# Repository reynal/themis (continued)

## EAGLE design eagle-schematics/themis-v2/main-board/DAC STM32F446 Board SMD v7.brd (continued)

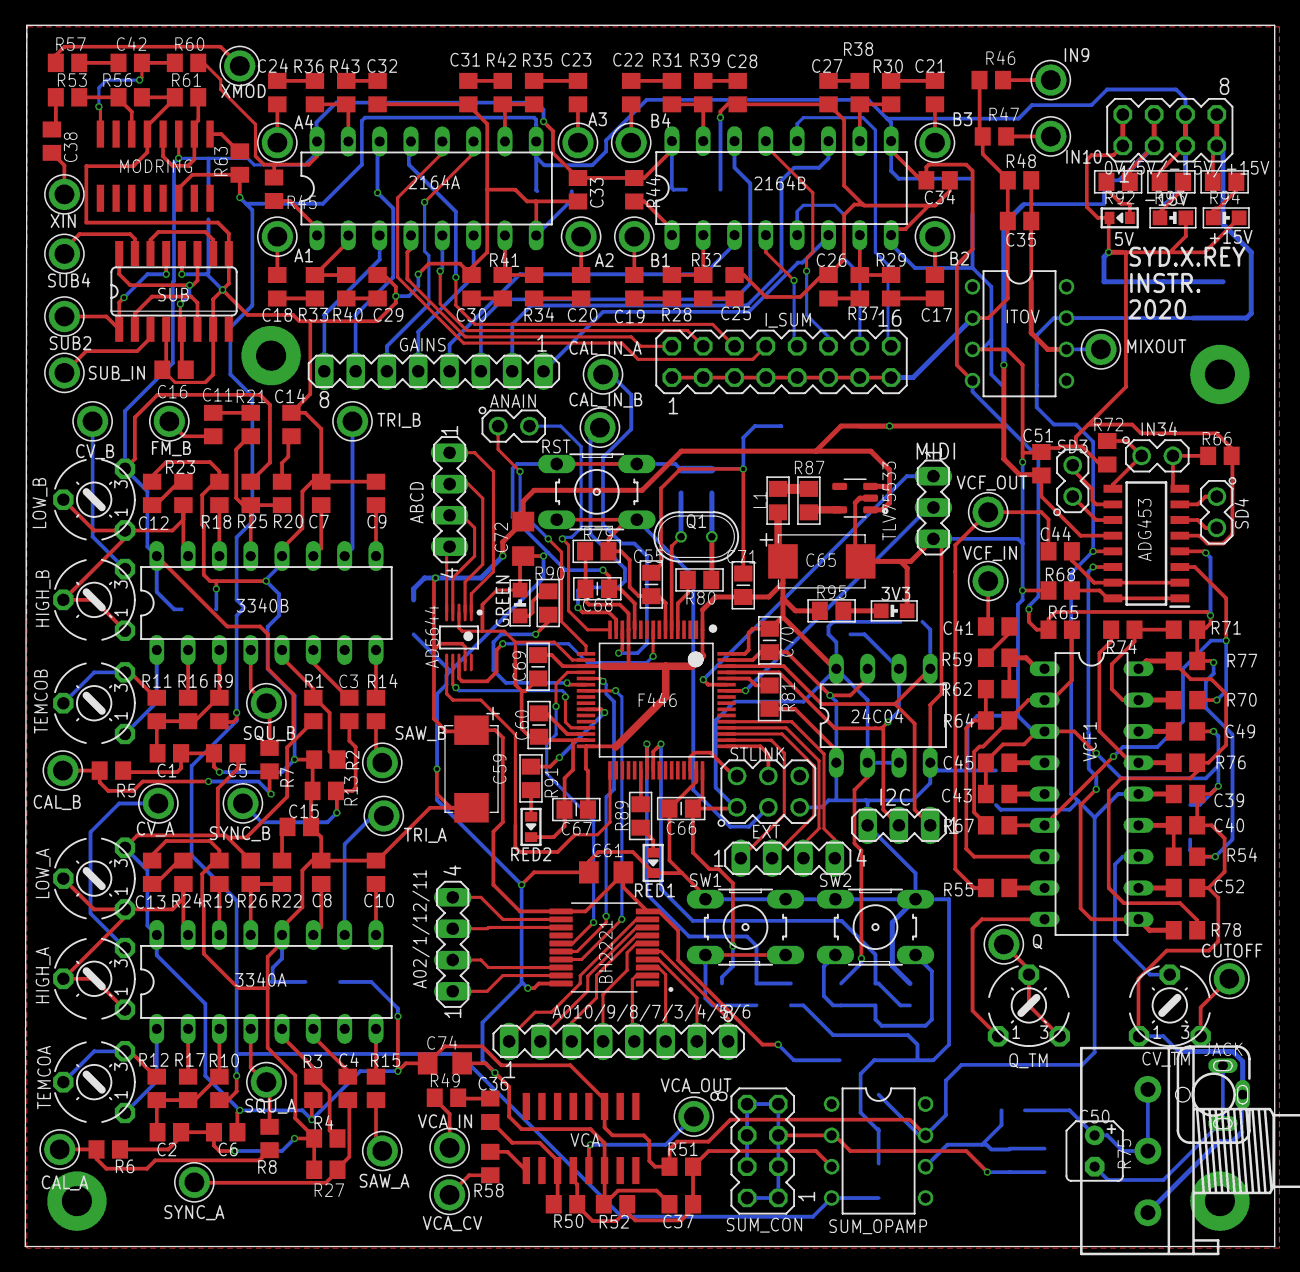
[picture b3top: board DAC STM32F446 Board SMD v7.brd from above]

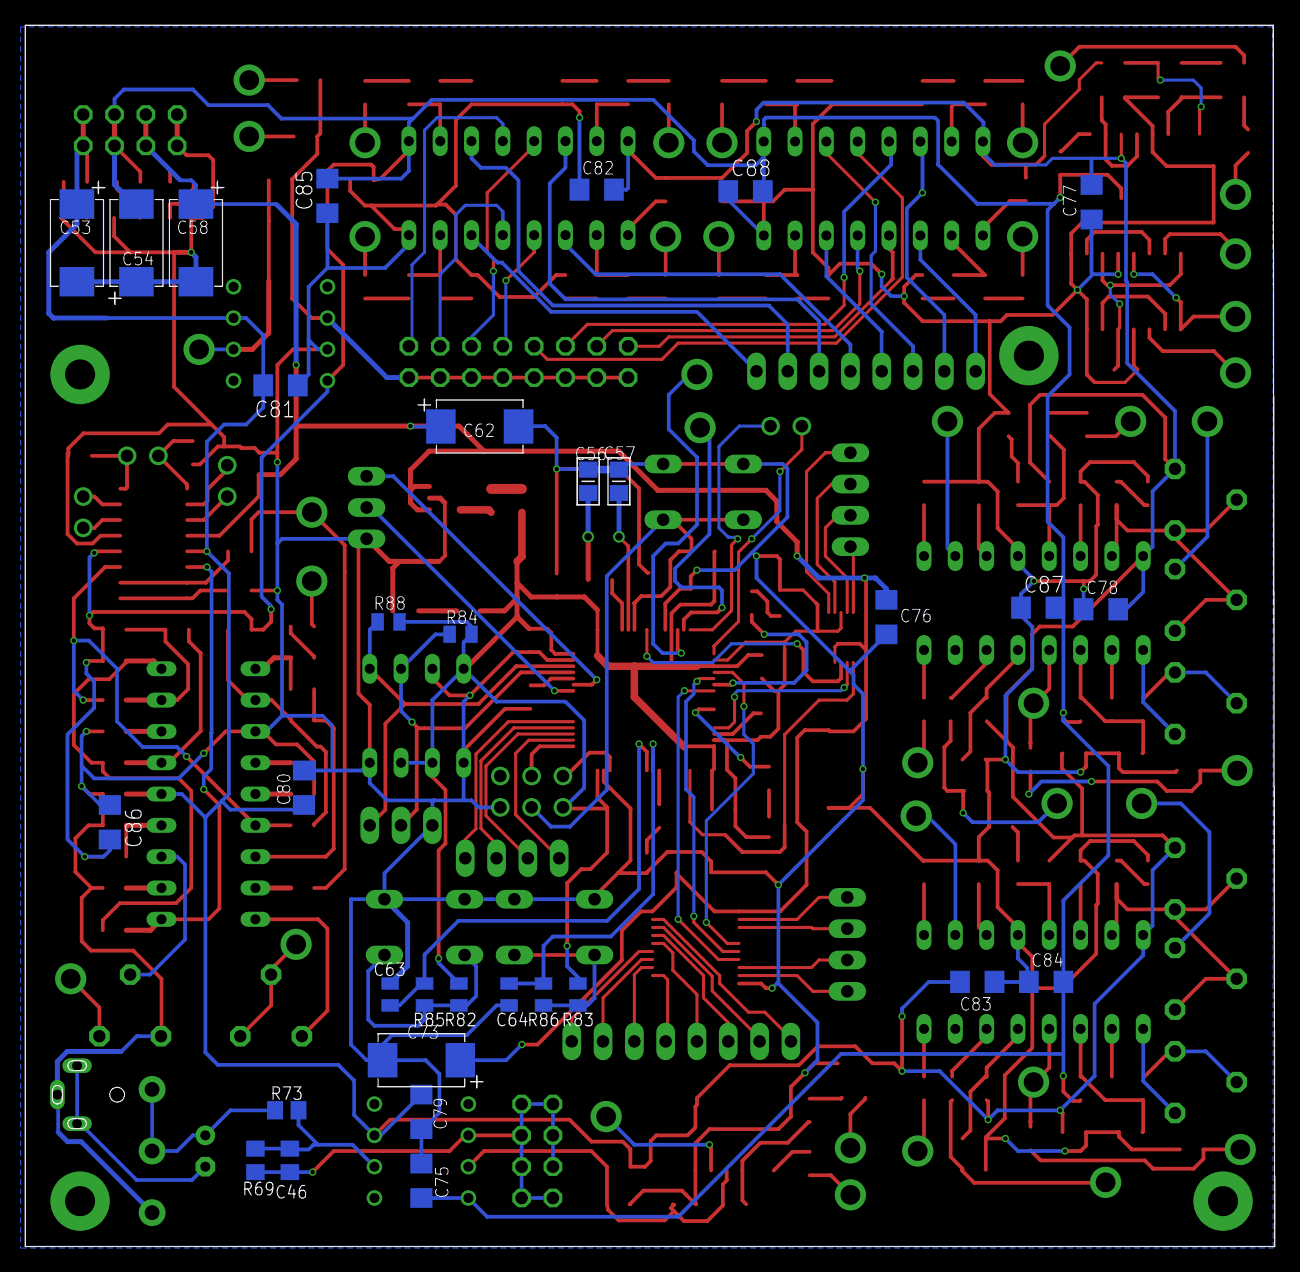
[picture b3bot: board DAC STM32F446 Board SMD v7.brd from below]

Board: 2 copper layers, 101.3 x 99.1 mm, 275 parts (32 on the bottom side), 213 nets.

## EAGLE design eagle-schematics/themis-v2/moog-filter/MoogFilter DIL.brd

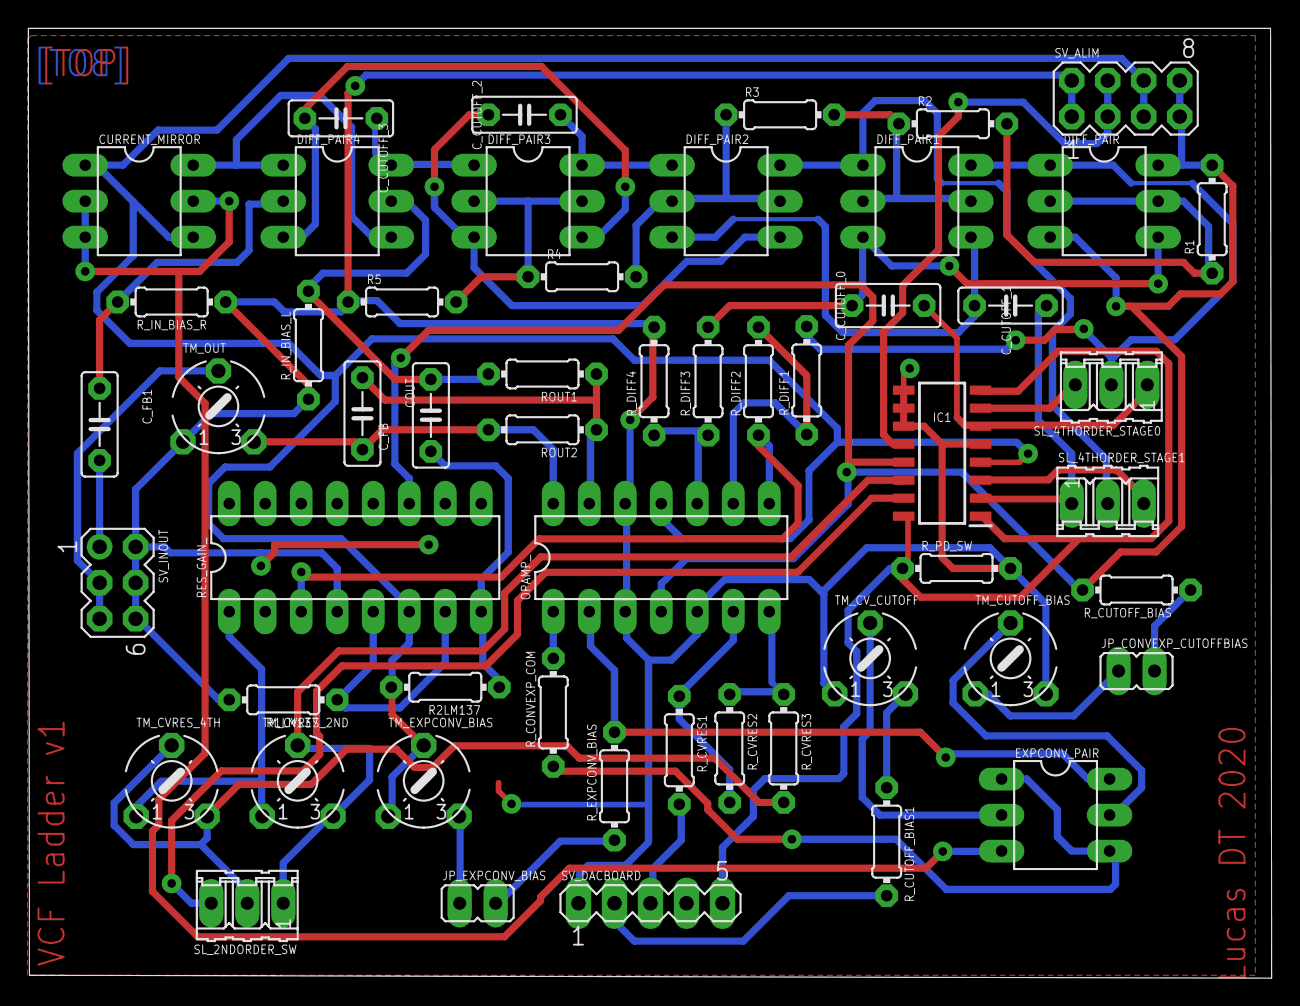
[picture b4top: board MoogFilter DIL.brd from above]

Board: 2 copper layers, 87.7 x 67.0 mm, 54 parts (0 on the bottom side), 52 nets.

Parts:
COUT: 470p; C5B2.5
CURRENT_MIRROR: BC846BDW1T1GDIL06; DIL06
C_CUTOFF_0: 220n; C5B3
C_CUTOFF_1, C_CUTOFF_2, C_CUTOFF_3: 220n; C5B2.5
C_FB, C_FB1: 10u; C5B2.5
DIFF_PAIR, DIFF_PAIR1, DIFF_PAIR2, DIFF_PAIR3, DIFF_PAIR4: BC846BDW1T1GDIL06; DIL06
EXPCONV_PAIR: BC857BS; DIL06
IC1: ADG453BRZ; SOIC127P600X175-16N
JP_CONVEXP_CUTOFFBIAS: JP1
JP_EXPCONV_BIAS: JP1
OPAMP_: TL084P; DIL14
R1, R2, R3, R4, R5: 1k; 0204/7
R1LM137, R2LM137: 22k; 0204/7
RES_GAIN_: LM13700N; DIL16
ROUT1, ROUT2: 10k; 0204/7
R_CONVEXP_COM: 220; 0204/7
R_CUTOFF_BIAS: 180k; 0204/7
R_CUTOFF_BIAS1: 12k; 0204/7
R_CVRES1: 10k; 0204/7
R_CVRES2: 56k; 0204/7
R_CVRES3: 22k; 0204/7
R_DIFF1, R_DIFF2, R_DIFF3, R_DIFF4: 10k; 0204/7
R_EXPCONV_BIAS: 100k; 0204/7
R_IN_BIAS_L: 1k; 0204/7
R_IN_BIAS_R: 1k; 0204/7
R_PD_SW: 100k; 0204/7
SL_2NDORDER_SW, SL_4THORDER_STAGE0, SL_4THORDER_STAGE1: 03P
SV_ALIM: MA04-2
SV_DACBOARD: MA05-1
SV_INOUT: MA03-2
TM_CUTOFF_BIAS: 1k; 6MM
TM_CVRES_2ND, TM_CVRES_4TH: 100k; 6MM
TM_CV_CUTOFF: 1k; 6MM
TM_EXPCONV_BIAS: 100k; 6MM
TM_OUT: 100k; 6MM

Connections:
2ND_4TH_ORDER_SW: IC1.1, IC1.8, IC1.16, R_PD_SW.1, SV_DACBOARD.5
5V: IC1.12, SV_ALIM.3, SV_ALIM.4
+15V: DIFF_PAIR.3, DIFF_PAIR.6, IC1.13, OPAMP_.4, R1.2, RES_GAIN_.11, R_CUTOFF_BIAS.2, SV_ALIM.7, SV_ALIM.8
-15V: CURRENT_MIRROR.1, CURRENT_MIRROR.4, IC1.4, OPAMP_.11, R2LM137.2, RES_GAIN_.6, SV_ALIM.5, SV_ALIM.6, TM_EXPCONV_BIAS.A, TM_EXPCONV_BIAS.S
B_0: DIFF_PAIR.2, DIFF_PAIR.5, R1.1, R2.2
B_1: DIFF_PAIR1.2, DIFF_PAIR1.5, R2.1, R3.2
B_2: DIFF_PAIR2.2, DIFF_PAIR2.5, R3.1, R4.2
B_3: DIFF_PAIR3.2, DIFF_PAIR3.5, R4.1, R5.2
CURRENT_CONTROL: CURRENT_MIRROR.2, CURRENT_MIRROR.3, CURRENT_MIRROR.5, EXPCONV_PAIR.3
CV_CUTOFF: R_CUTOFF_BIAS1.2, SV_DACBOARD.2
CV_RES: R_CVRES1.2, SV_DACBOARD.3
GND: IC1.5, IC1.9, IC1.10, IC1.11, OPAMP_.3, OPAMP_.5, OPAMP_.12, R1LM137.2, R5.1, RES_GAIN_.4, R_DIFF4.2, R_IN_BIAS_L.1, R_IN_BIAS_R.1, R_PD_SW.2, SV_ALIM.1, SV_ALIM.2, SV_DACBOARD.1, SV_INOUT.2, SV_INOUT.4, SV_INOUT.6, TM_CUTOFF_BIAS.E, TM_CV_CUTOFF.A, TM_OUT.A
I_ABC: RES_GAIN_.1, TM_CVRES_2ND.A, TM_CVRES_4TH.A
LM13700_BUF: C_FB.1, R2LM137.1, RES_GAIN_.8
LM13700_IN+: OPAMP_.8, RES_GAIN_.3, R_DIFF2.1
LM13700_IOUT: R1LM137.1, RES_GAIN_.5, RES_GAIN_.7
unnamed: COUT.1, OPAMP_.13, ROUT1.1, ROUT2.1
unnamed: EXPCONV_PAIR.1, EXPCONV_PAIR.4, R_CONVEXP_COM.1
unnamed: JP_CONVEXP_CUTOFFBIAS.2, R_CUTOFF_BIAS.1
unnamed: OPAMP_.1, R_CONVEXP_COM.2
unnamed: JP_CONVEXP_CUTOFFBIAS.1, TM_CUTOFF_BIAS.A
unnamed: CURRENT_MIRROR.6, DIFF_PAIR4.1, DIFF_PAIR4.4
unnamed: EXPCONV_PAIR.6, OPAMP_.2, R_EXPCONV_BIAS.2
unnamed: JP_EXPCONV_BIAS.2, R_EXPCONV_BIAS.1
unnamed: OPAMP_.6, R_CVRES1.1, R_CVRES2.2
unnamed: OPAMP_.7, R_CVRES2.1, R_CVRES3.1
unnamed: OPAMP_.10, R_DIFF3.1, R_DIFF4.1
unnamed: OPAMP_.9, R_DIFF1.1, R_DIFF2.2
unnamed: COUT.2, OPAMP_.14, ROUT2.2, TM_OUT.E
unnamed: JP_EXPCONV_BIAS.1, TM_EXPCONV_BIAS.E
unnamed: R_CVRES3.2, SL_2NDORDER_SW.2, TM_CVRES_4TH.E, TM_CVRES_4TH.S
unnamed: R_CUTOFF_BIAS1.1, TM_CV_CUTOFF.E
OUT: SV_INOUT.3, SV_INOUT.5, TM_OUT.S
OUT_L_4TH: C_CUTOFF_0.1, DIFF_PAIR.4, DIFF_PAIR1.3, R_DIFF3.2
OUT_R_4TH: DIFF_PAIR.1, DIFF_PAIR1.6, R_DIFF1.2, SL_4THORDER_STAGE0.2
Q2A_E: C_CUTOFF_1.1, DIFF_PAIR1.4, DIFF_PAIR2.3
Q2B_E: DIFF_PAIR1.1, DIFF_PAIR2.6, SL_4THORDER_STAGE1.2
Q3A_E: C_CUTOFF_2.1, DIFF_PAIR2.4, DIFF_PAIR3.3
Q3B_E: C_CUTOFF_2.2, DIFF_PAIR2.1, DIFF_PAIR3.6
Q4A_E: C_CUTOFF_3.1, DIFF_PAIR3.4, DIFF_PAIR4.3
Q4B_E: C_CUTOFF_3.2, DIFF_PAIR3.1, DIFF_PAIR4.6
STAGE0_L: C_CUTOFF_0.2, IC1.6, SL_4THORDER_STAGE0.1
STAGE0_R: IC1.7, SL_4THORDER_STAGE0.3
STAGE1_L: IC1.3, SL_4THORDER_STAGE1.3
STAGE1_R: C_CUTOFF_1.2, IC1.2, SL_4THORDER_STAGE1.1
SW_2ND_ORDER_A: IC1.15, SL_2NDORDER_SW.3
SW_2ND_ORDER_B: IC1.14, SL_2NDORDER_SW.1, TM_CVRES_2ND.E, TM_CVRES_2ND.S
T_EXPCONV_B1: EXPCONV_PAIR.2, TM_CV_CUTOFF.S
T_EXPCONV_B2: EXPCONV_PAIR.5, TM_CUTOFF_BIAS.S
VIN: C_FB1.2, SV_INOUT.1
VIN_L: C_FB.2, DIFF_PAIR4.5, ROUT1.2, R_IN_BIAS_L.2
VIN_R: C_FB1.1, DIFF_PAIR4.2, R_IN_BIAS_R.2

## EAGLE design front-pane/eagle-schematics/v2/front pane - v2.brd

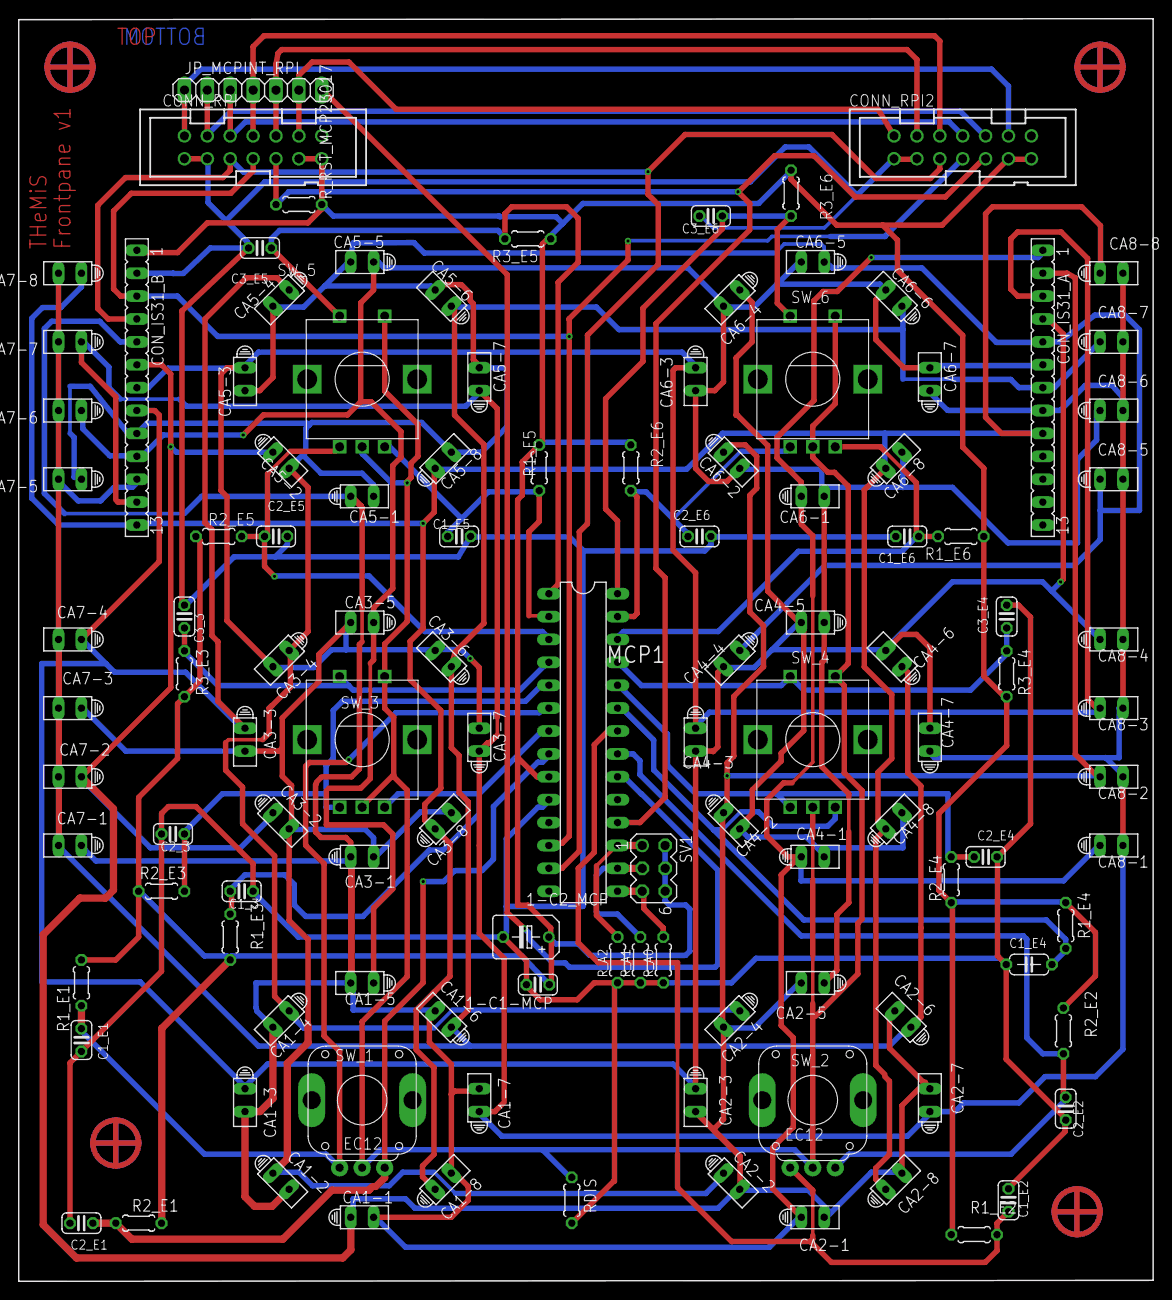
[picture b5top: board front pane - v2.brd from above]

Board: 2 copper layers, 125.9 x 140.1 mm, 116 parts (0 on the bottom side), 41 nets.

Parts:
1-C1-MCP: 100n; C025-024X044
1-C2_MCP: 10u; B45181B
C1_3, C1_E1, C1_E2, C1_E5, C1_E6, C2_3, C2_E1, C2_E2, C2_E4, C2_E5, C2_E6, C3_3, C3_E4, C3_E5, C3_E6: 100n; C025-024X044
C1_E4: 100n; C050-024X044
CA1-1, CA1-2, CA1-3, CA1-4, CA1-5, CA1-6, CA1-7, CA1-8, CA2-1, CA2-2, CA2-3, CA2-4, CA2-5, CA2-6, CA2-7, CA2-8, CA3-1, CA3-2, CA3-3, CA3-4, CA3-5, CA3-6, CA3-7, CA3-8, CA4-1, CA4-2, CA4-3, CA4-4, CA4-5, CA4-6, CA4-7, CA4-8, CA5-1, CA5-2, CA5-3, CA5-4, CA5-5, CA5-6, CA5-7, CA5-8, CA6-1, CA6-2, CA6-3, CA6-4, CA6-5, CA6-6, CA6-7, CA6-8, CA7-1, CA7-2, CA7-3, CA7-4, CA7-5, CA7-6, CA7-7, CA7-8, CA8-1, CA8-2, CA8-3, CA8-4, CA8-5, CA8-6, CA8-7, CA8-8: HLMP6
CONN_RPI, CONN_RPI2: 2514-; PAK100/2500-14
CON_IS31_A, CON_IS31_B: FE13
JP_MCPINT_RPI: 1X07
MCP1: MCP23017SP; DIL28-3
R1_E1, R1_E2, R1_E3, R1_E4, R1_E5, R1_E6, R2_E1, R2_E2, R2_E3, R2_E4, R2_E5, R2_E6, R3_E3, R3_E4, R3_E5, R3_E6: 100k; 0204/5
RDIS: 1k; 0204/5
R_A0, R_A1, R_A2: 20k; 0204/5
R_RST_MCP23017: 100k; 0204/5
SV1: MA03-2
SW_1, SW_2: EC12
SW_3, SW_4, SW_5, SW_6: EC12E_SW; ALPS_EC12E_SW

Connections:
A0: MCP1.15, R_A0.2, SV1.5
A1: MCP1.16, R_A1.2, SV1.3
A2: MCP1.17, R_A2.2, SV1.1
CA1: CA1-1.K, CA1-2.K, CA1-3.K, CA1-4.K, CA1-5.K, CA1-6.K, CA1-7.K, CA1-8.K, CA2-1.A, CA3-1.A, CA4-1.A, CA5-1.A, CA6-1.A, CA7-1.A, CA8-1.A, CON_IS31_A.1, CON_IS31_B.5
CA2: CA1-1.A, CA2-1.K, CA2-2.K, CA2-3.K, CA2-4.K, CA2-5.K, CA2-6.K, CA2-7.K, CA2-8.K, CA3-2.A, CA4-2.A, CA5-2.A, CA6-2.A, CA7-2.A, CA8-2.A, CON_IS31_A.2, CON_IS31_B.6
CA3: CA1-2.A, CA2-2.A, CA3-1.K, CA3-2.K, CA3-3.K, CA3-4.K, CA3-5.K, CA3-6.K, CA3-7.K, CA3-8.K, CA4-3.A, CA5-3.A, CA6-3.A, CA7-3.A, CA8-3.A, CON_IS31_A.3, CON_IS31_B.7
CA4: CA1-3.A, CA2-3.A, CA3-3.A, CA4-1.K, CA4-2.K, CA4-3.K, CA4-4.K, CA4-5.K, CA4-6.K, CA4-7.K, CA4-8.K, CA5-4.A, CA6-4.A, CA7-4.A, CA8-4.A, CON_IS31_A.4, CON_IS31_B.8
CA5: CA1-4.A, CA2-4.A, CA3-4.A, CA4-4.A, CA5-1.K, CA5-2.K, CA5-3.K, CA5-4.K, CA5-5.K, CA5-6.K, CA5-7.K, CA5-8.K, CA6-5.A, CA7-5.A, CA8-5.A, CON_IS31_A.5, CON_IS31_B.9
CA6: CA1-5.A, CA2-5.A, CA3-5.A, CA4-5.A, CA5-5.A, CA6-1.K, CA6-2.K, CA6-3.K, CA6-4.K, CA6-5.K, CA6-6.K, CA6-7.K, CA6-8.K, CA7-6.A, CA8-6.A, CON_IS31_A.6, CON_IS31_B.10
CA7: CA1-6.A, CA2-6.A, CA3-6.A, CA4-6.A, CA5-6.A, CA6-6.A, CA7-1.K, CA7-2.K, CA7-3.K, CA7-4.K, CA7-5.K, CA7-6.K, CA7-7.K, CA7-8.K, CA8-7.A, CON_IS31_A.7, CON_IS31_B.11
CA8: CA1-7.A, CA2-7.A, CA3-7.A, CA4-7.A, CA5-7.A, CA6-7.A, CA7-7.A, CA8-1.K, CA8-2.K, CA8-3.K, CA8-4.K, CA8-5.K, CA8-6.K, CA8-7.K, CA8-8.K, CON_IS31_A.8, CON_IS31_B.12
CA9: CA1-8.A, CA2-8.A, CA3-8.A, CA4-8.A, CA5-8.A, CA6-8.A, CA7-8.A, CA8-8.A, CON_IS31_A.9, CON_IS31_B.13
DISCHARGE: RDIS.1, SW_1.2, SW_2.2, SW_3.C, SW_3.E, SW_4.C, SW_4.E, SW_5.C, SW_5.E, SW_6.C, SW_6.E
GND: 1-C1-MCP.2, 1-C2_MCP.-, C1_3.2, C1_E1.2, C1_E2.2, C1_E4.2, C1_E5.2, C1_E6.2, C2_3.2, C2_E1.2, C2_E2.2, C2_E4.2, C2_E5.2, C2_E6.2, C3_3.2, C3_E4.2, C3_E5.2, C3_E6.2, CONN_RPI.1, CONN_RPI.3, CONN_RPI2.1, CONN_RPI2.3, CON_IS31_B.2, MCP1.10, RDIS.2, R_A0.1, R_A1.1, R_A2.1
GPA0: C2_E2.1, MCP1.21, R2_E2.2, SW_2.3
GPA1: C1_E2.1, MCP1.22, R1_E2.2, SW_2.1
GPA2: C1_E4.1, MCP1.23, R1_E4.2, SW_4.B
GPA3: C2_E4.1, MCP1.24, R2_E4.2, SW_4.A
GPA4: C3_E4.1, MCP1.25, R3_E4.2, SW_4.D
GPA5: C1_E6.1, MCP1.26, R1_E6.2, SW_6.B
GPA6: C2_E6.1, MCP1.27, R2_E6.2, SW_6.A
GPA7: C3_E6.1, MCP1.28, R3_E6.2, SW_6.D
GPB0: C3_E5.1, MCP1.1, R3_E5.2, SW_5.D
GPB1: C1_E5.1, MCP1.2, R1_E5.2, SW_5.B
GPB2: C2_E5.1, MCP1.3, R2_E5.2, SW_5.A
GPB3: C3_3.1, MCP1.4, R3_E3.2, SW_3.D
GPB4: C2_3.1, MCP1.5, R2_E3.2, SW_3.A
GPB5: C1_E1.1, MCP1.6, R1_E1.2, SW_1.1
GPB6: C1_3.1, MCP1.7, R1_E3.2, SW_3.B
GPB7: C2_E1.1, MCP1.8, R2_E1.2, SW_1.3
INTA: CONN_RPI.2, CONN_RPI2.12, JP_MCPINT_RPI.1
INTB: CONN_RPI.4, CONN_RPI2.10, JP_MCPINT_RPI.2
INTC: CONN_RPI.6, CONN_RPI2.8, JP_MCPINT_RPI.3
INTD: CONN_RPI.8, CONN_RPI2.6, JP_MCPINT_RPI.4
INTE: CONN_RPI.10, CONN_RPI2.4, JP_MCPINT_RPI.5
INTF: CONN_RPI.12, CONN_RPI2.2, JP_MCPINT_RPI.6
INT_MCP23017_1: JP_MCPINT_RPI.7, MCP1.20
RST_MCP: CONN_RPI.9, CONN_RPI2.9, MCP1.18, R_RST_MCP23017.2
SCL: CONN_RPI.7, CONN_RPI2.7, CON_IS31_B.3, MCP1.12
SDA: CONN_RPI.5, CONN_RPI2.5, CON_IS31_B.4, MCP1.13
VCC: 1-C1-MCP.1, 1-C2_MCP.+, CONN_RPI.11, CONN_RPI.13, CONN_RPI2.11, CONN_RPI2.13, CON_IS31_B.1, MCP1.9, R1_E1.1, R1_E2.1, R1_E3.1, R1_E4.1, R1_E5.1, R1_E6.1, R2_E1.1, R2_E2.1, R2_E3.1, R2_E4.1, R2_E5.1, R2_E6.1, R3_E3.1, R3_E4.1, R3_E5.1, R3_E6.1, R_RST_MCP23017.1, SV1.2, SV1.4, SV1.6
